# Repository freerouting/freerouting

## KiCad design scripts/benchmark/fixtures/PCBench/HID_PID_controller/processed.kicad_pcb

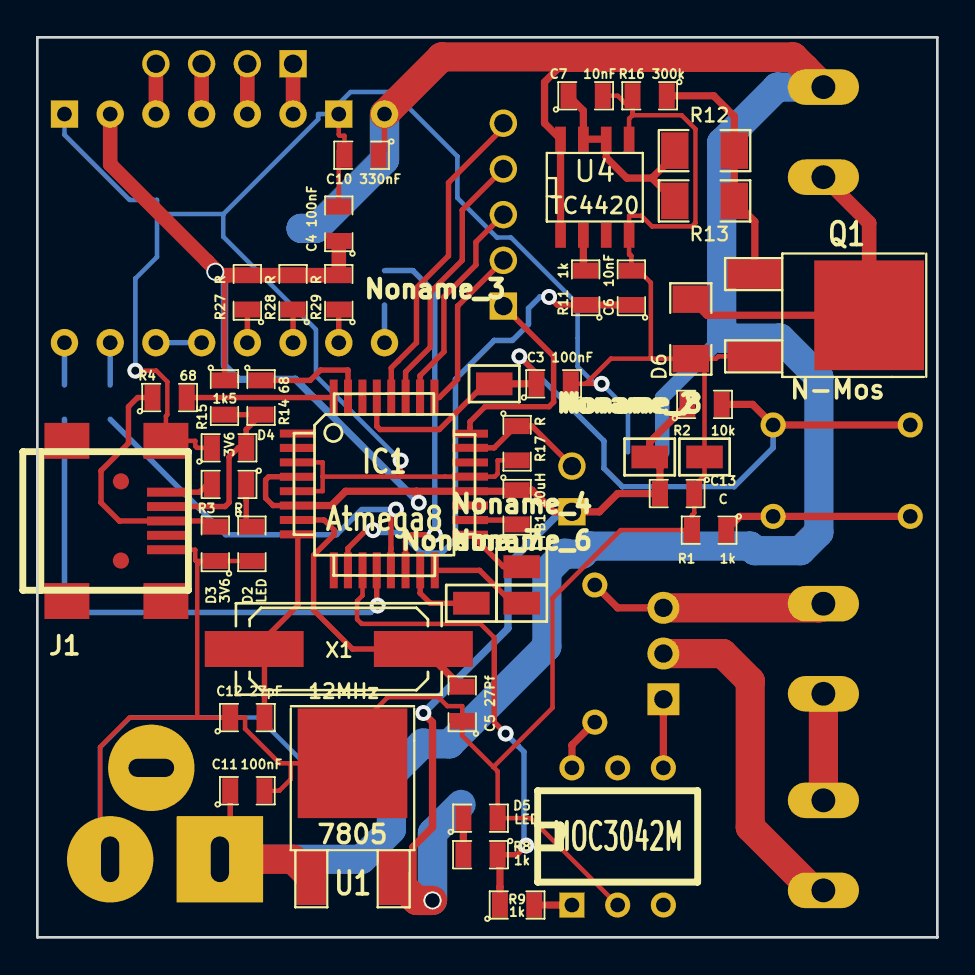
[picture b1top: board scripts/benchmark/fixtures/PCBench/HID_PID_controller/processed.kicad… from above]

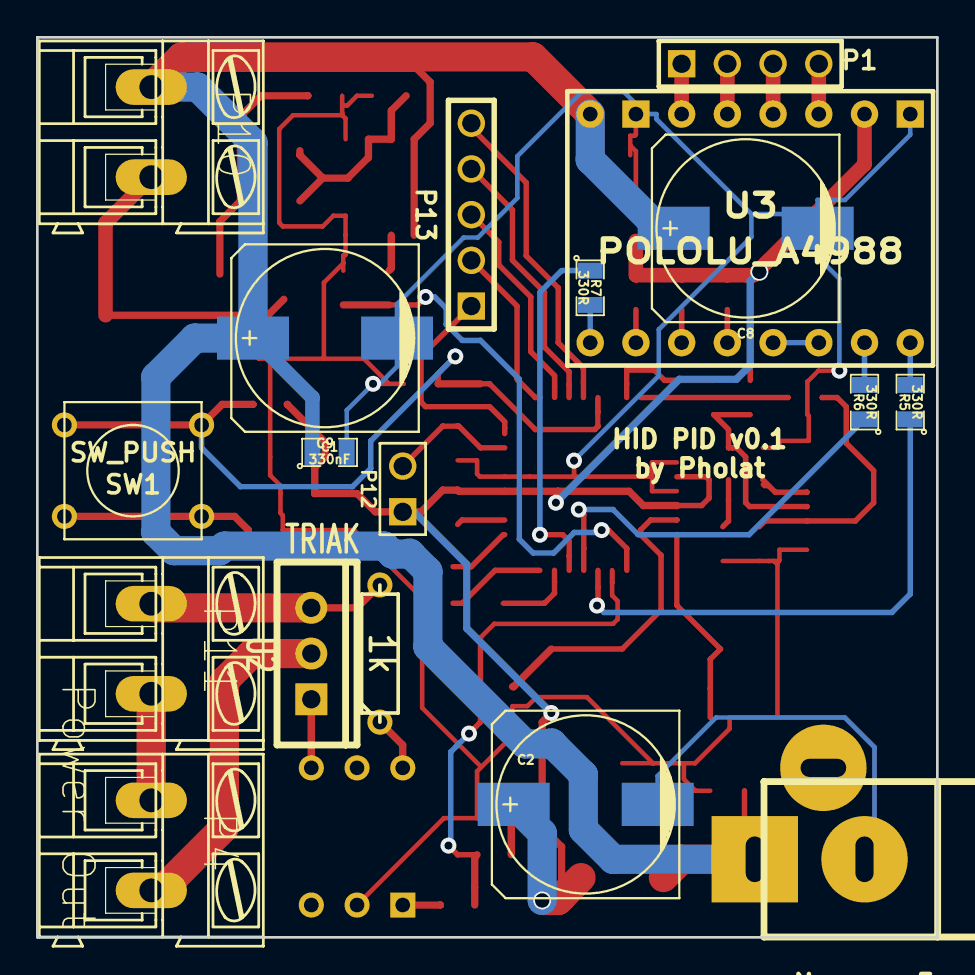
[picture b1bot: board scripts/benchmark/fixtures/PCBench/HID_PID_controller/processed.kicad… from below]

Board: 2 copper layers, 50.0 x 50.0 mm, 62 parts (18 on the bottom side), 50 nets.

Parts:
C1, C10: 330nF; SM0805
C2, C8, C9: 330uF; c_elec_10x10.5
C3, C4, C11: 100nF; SM0805
C5: 27Pf; SM0805
C6, C7: 10nF; SM0805
C12: 27pF; SM0805
C13: C; SM0805
D2, D5: LED; SM0805
D3, D4: 3V6; SM0805
D6: DIODE; SM1206
FB1: 10uH; SM0805
IC1: Atmega8; TQFP32
J1: USB; USB_MINI_B
Noname_1: MOC3042M; DIP-6__300
Noname_2, Noname_3, Noname_4, Noname_6, Noname_7, Noname_8: SMD_PIN
Noname_5: JACK_ALIM
P1: PIN_ARRAY_4x1
P4: Power Out; AK300-2
P10, P11: AK300-2
P12: NTC; PIN_ARRAY_2X1
P13: CONN_5; PIN_ARRAY_5x1
Q1: N-Mos; DPAKGDS
R1, R8, R9, R11: 1k; SM0805
R2: 10k; SM0805
R3, R17, R27, R28, R29: R; SM0805
R4, R14: 68; SM0805
R5, R6, R7: 330R; SM0805
R10: 1k; R3
R12, R13: 47; SM1206
R15: 1k5; SM0805
R16: 300k; SM0805
SW1: SW_PUSH; SW_PUSH_SMALL
U1: 7805; DPAK2
U2: TRIAK; TO220_VERT
U3: POLOLU_A4988; SWDIP8_.6W
U4: TC4420; SO8E
X1: 12MHz; Q_49U3HMS

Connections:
/AC_Controll: IC1.11, R8.1, R9.1
/AVcc: FB1.2, IC1.18
/D+: D3.2, J1.3, R4.1
/D-: D4.2, J1.2, R14.2, R15.2
/DIR1: R5.2, U3.16
/EN1: R7.2, U3.9
/MISO: IC1.16, Noname_6.1
/MOSI: IC1.15, Noname_7.1
/PWM: C6.1, IC1.10, R11.1
/RES: C3.1, IC1.29, Noname_3.1, R2.2, SW1.2
/SCK: IC1.17, Noname_4.1
/STEP1: R6.2, U3.15
/TempCheck: IC1.23, P12.2, R17.1
GND: C1.2, C2.2, C3.2, C4.2, C5.1, C6.2, C7.2, C8.2, C9.2, C10.2, C11.2, C12.1, C13.1, D2.2, D3.1, D4.1, D5.2, D6.1, IC1.3, IC1.5, IC1.21, J1.5, J1.6, Noname_1.2, Noname_2.1, Noname_5.2, Q1.S, R1.2, R16.2, R17.2, U1.2, U3.1, U3.7, U4.4, U4.5
unnamed: C12.2, IC1.8, X1.1
unnamed: P4.2, U2.3
unnamed: P4.1, P11.2
unnamed: IC1.25, P13.2
unnamed: IC1.28, P13.5
unnamed: IC1.27, P13.4
unnamed: IC1.24, P13.1
unnamed: IC1.32, R4.2
unnamed: D6.2, P10.2, Q1.D
unnamed: C7.1, R12.1, R13.1, U4.6, U4.7
unnamed: R11.2, U4.2
unnamed: Q1.G, R12.2, R13.2, R16.1
unnamed: IC1.31, R14.1
unnamed: R1.1, SW1.1
unnamed: IC1.26, P13.3
unnamed: C5.2, IC1.7, X1.2
unnamed: IC1.14, R7.1
unnamed: IC1.13, R6.1
unnamed: IC1.12, R5.1
unnamed: D2.1, R3.1
unnamed: J1.1, R3.2
unnamed: R27.1, U3.12
unnamed: R28.1, U3.11
unnamed: R29.1, U3.10
unnamed: P1.1, U3.6
unnamed: P1.2, U3.5
unnamed: P1.3, U3.4
unnamed: P1.4, U3.3
unnamed: P11.1, R10.2, U2.2
unnamed: Noname_1.6, R10.1
unnamed: Noname_1.4, U2.1
unnamed: Noname_1.1, R9.2
unnamed: D5.1, R8.2
unnamed: U3.13, U3.14
VAA: C1.1, C8.1, C9.1, C10.1, C11.1, Noname_5.1, P10.1, U1.1, U3.8, U4.1, U4.8
VCC: C2.1, C4.1, C13.2, FB1.1, IC1.4, IC1.6, IC1.20, Noname_8.1, P12.1, R2.1, R15.1, R27.2, R28.2, R29.2, U1.3, U3.2

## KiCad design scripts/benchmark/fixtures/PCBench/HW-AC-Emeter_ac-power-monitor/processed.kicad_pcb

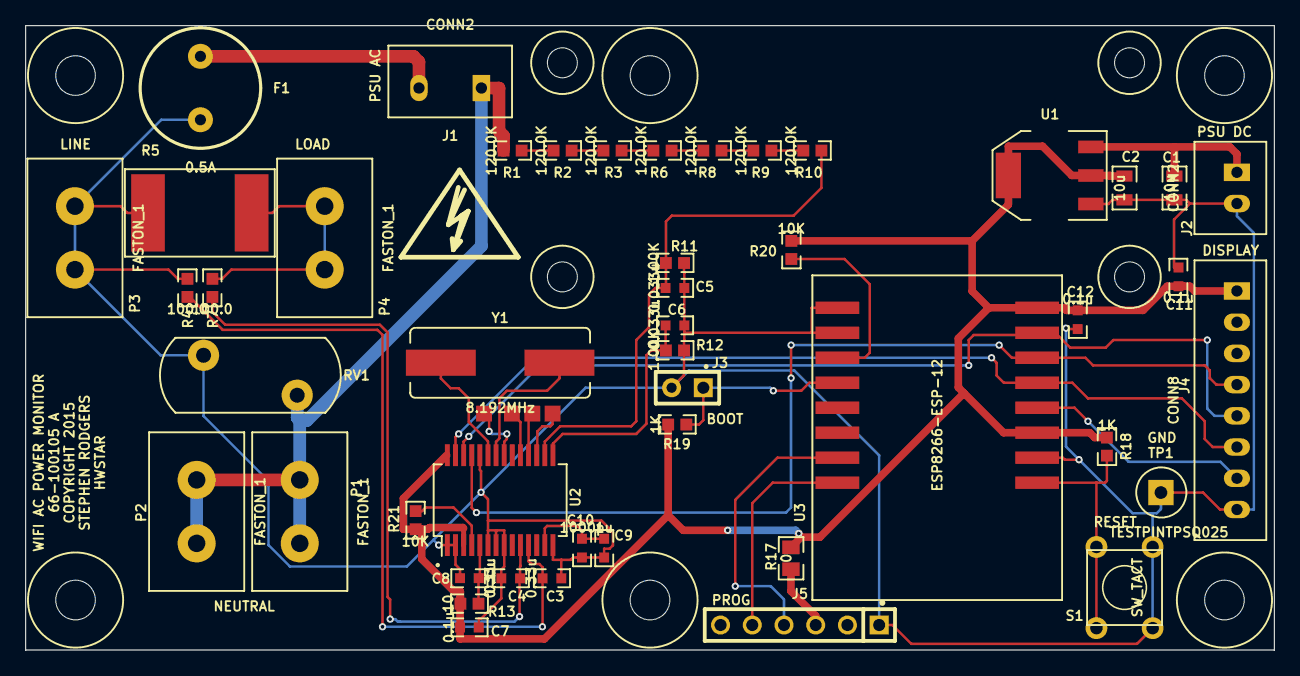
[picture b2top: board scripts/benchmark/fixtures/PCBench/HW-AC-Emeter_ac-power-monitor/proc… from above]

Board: 2 copper layers, 100.0 x 50.0 mm, 62 parts (0 on the bottom side), 35 nets.

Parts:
C1, C2: 10u; CC0805
C3, C4: 0.33u; CC0603
C5, C6: 0.033u; CC0603
C7, C8, C11, C12: 0.1u; CC0603
C9: 1u; CC0603
C10: 1000p; CC0603
F1: 0.5A; BELFUSE_MRT
J1: CONN2; JST_B3B_SPECIAL
J2: CONN2; JST_B2B_XH_A
J3: CONN2; BERG2
J4: CONN8; JST_B8B_XH_A
J5: CONN6; BERG6
MTG-HOLE-125-RING-300, MTG-HOLE-125-RING-300_2, MTG-HOLE-125-RING-300_3, MTG-HOLE-125-RING-300_4, MTG-HOLE-125-RING-300_5, MTG-HOLE-125-RING-300_6: VAL**; MTG-HOLE-125-RING-300
MTG-HOLE-M2-RING-5MM, MTG-HOLE-M2-RING-5MM_2, MTG-HOLE-M2-RING-5MM_3, MTG-HOLE-M2-RING-5MM_4: VAL**; MTG-HOLE-M2-RING-5MM
P1, P2, P3, P4: FASTON_1; KEYSTONE_1287-ST
R1, R2, R3, R6, R8, R9, R10: 120.0K; RC0603
R4, R7: 100.0; RC0603
R5: 0.001; WSL3921
R11, R12: 1.00K; RC0603
R13: 10; RC0603
R17: 0; RC0805
R18, R19: 1K; RC0603
R20, R21: 10K; RC0603
RV1: MOV-10D431; VARISTOR-10D
S1: SW_TACT; SW_TACT_6MM
Sym: Symbol_HighVoltage_Type2_SilkTop_VerySmall
TP1: TESTPINTPSQ025; TESTPIN
TP2, TP3, TP4, TP5: TESTPINTPSQ025; TESTPAD
U1: AZ1117CH-3.3TRG1; SOT-223-SAR
U2: 90E24PYGI; SSOP28-SAR
U3: ESP8266-ESP-12; ESP8266-ESP12
Y1: 8.192MHz; HC49US-SAR

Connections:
+3.3V: C2.1, C7.1, C11.1, C12.1, J4.1, R13.1, R17.1, R18.1, R19.1, R20.1, R21.1, U1.2, U1.4, U2.3, U2.28, U3.3, U3.8
/Power/+5V: C1.1, J2.1, U1.3
/Power/HOT: F1.2, J1.2
/Power/LOAD: P4.1, P4.2, R5.2, R7.2
/Power/NEUTRAL: J1.1, P1.1, P1.2, P2.1, P2.2, R1.1, RV1.1
/WIFI/GPIO16: J4.7, U3.4
/WIFI/SPWR: J5.3, R17.2
GND: C1.2, C2.2, C3.2, C4.1, C5.2, C6.2, C7.2, C8.2, C9.2, C10.2, C11.2, C12.2, F1.1, J2.2, J3.2, J4.8, J5.1, P3.1, P3.2, R4.2, R5.1, R11.2, R12.2, RV1.2, S1.1, S1.2, TP1.1, U1.1, U2.1, U2.2, U2.6, U2.7, U2.8, U2.14, U2.24, U3.2, U3.9, U3.10
ISAMPLEN: C3.1, R4.1, U2.11
ISAMPLEP: C4.2, R7.1, U2.10
unnamed: C8.1, R13.2, U2.5
unnamed: C9.1, C10.1, U2.13
unnamed: J3.1, R19.2, U3.12
unnamed: J5.4, U3.15
unnamed: J5.5, U3.16
unnamed: R1.2, R2.1
unnamed: R2.2, R3.1
unnamed: R3.2, R6.1
unnamed: R6.2, R8.1
unnamed: R8.2, R9.1
unnamed: R9.2, R10.1
unnamed: R18.2, S1.3, S1.4, U3.1
unnamed: R20.2, U3.11
unnamed: R21.2, U2.4
unnamed: TP2.1, U2.18
unnamed: TP3.1, U2.19
unnamed: TP4.1, U2.21
unnamed: TP5.1, U2.17
unnamed: U2.22, Y1.2
unnamed: U2.23, Y1.1
SCLK: J4.4, U2.25, U3.6
SDI: J4.6, U2.27, U3.5
SDO: J4.5, U2.26, U3.7
VSAMPLEN: C6.1, R12.1, U2.15
VSAMPLEP: C5.1, R10.2, R11.1, U2.16

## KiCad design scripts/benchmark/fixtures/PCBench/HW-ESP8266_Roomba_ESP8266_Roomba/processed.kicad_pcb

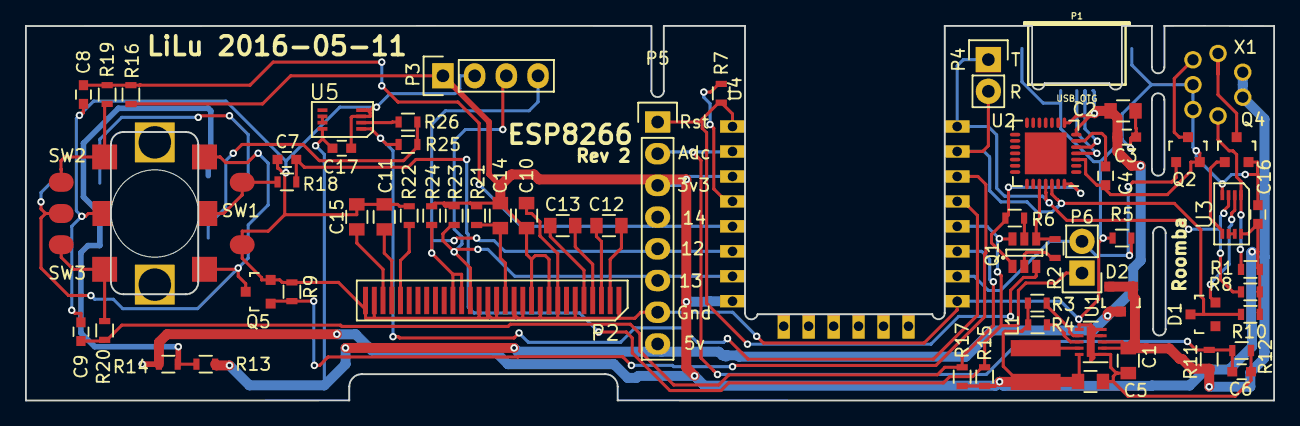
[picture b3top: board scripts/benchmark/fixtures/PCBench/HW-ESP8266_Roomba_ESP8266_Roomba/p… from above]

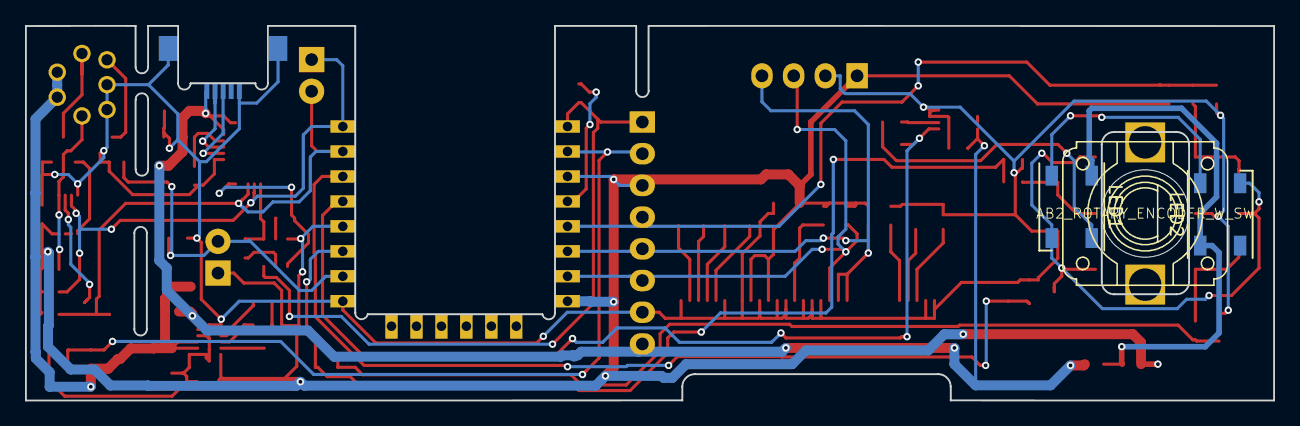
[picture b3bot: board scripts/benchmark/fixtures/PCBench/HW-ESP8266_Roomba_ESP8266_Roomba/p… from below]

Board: 2 copper layers, 100.0 x 30.0 mm, 68 parts (3 on the bottom side), 50 nets.

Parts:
C1, C11, C14, C15: 2u2; C_0805
C2, C10, C12, C13: 1u; C_0805
C3, C4, C6, C7, C8, C9, C16, C17: 100n; C_0603
C5: 22u; C_0805
D1, D2: MMBD717LT1G; SOT-23
L1: VLS4012ET-100M
LED1, LED2: WS2812B; LED_WS2812B-PLCC4
P1: USB_OTG; conn_usb_B_micro_smd-backside
P2: UG_62864
P3: CONN_01X04; Pin_Header_Straight_1x04
P4, P6: CONN_01X02; Pin_Header_Straight_1x02
P5: CONN_01X08; Pin_Header_Straight_1x08
Q1: DMC204010R; SOT-23-6
Q2, Q4, Q5: 2N7002; SOT-23
R1: 1M; R_0603
R2, R6, R7, R15, R16, R17, R21, R23, R24: 10k; R_0603
R3, R4, R5, R8, R9, R10: 100k; R_0603
R11: 470k; R_0603
R12: 18k; R_0603
R13, R14, R25, R26: 0R; R_0603
R18, R19, R20: 1k; R_0603
R22: 390k; R_0603
ROT_ENC1: AB2_ROTARY_ENCODER_W_SW; ROT_ENC_backside
SW1, SW2, SW3: SW_PUSH; switch3x6_smd
U1: TPS62177; DFN-10-1EP_2x3mm_Pitch0.5mm
U2: CP2102; QFN-28-1EP_5x5mm_Pitch0.5mm
U3, U5: 74LVC3G14; VSSOP-8
U4: ESP-12E; ESP-12E_SideMounted
X1: MINI_DIN_7; MiniDin-7

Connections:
+3V3: C5.1, C10.1, C14.1, C16.1, L1.2, P2.9, P2.11, P3.1, P5.3, R1.2, R3.1, R4.1, R8.1, R10.1, R14.1, R15.2, R16.2, R17.2, R21.2, R23.2, R24.2, U1.10, U3.8, U4.8
+12V: C1.1, D2.1, D2.2, R11.1, U1.2, U1.3, X1.1, X1.2
/5V: C2.1, C3.1, C17.1, D2.3, P1.1, P5.8, R13.2, U2.7, U2.8, U5.8
/ADC: C6.1, P5.2, R11.2, R12.1, U4.2
/DTR: Q1.1, R6.1, U2.28
/Enc_A: C9.1, R17.1, R20.2, U4.17
/Enc_B: C8.1, P5.4, R16.1, R19.2, U4.5
/LED: R25.2, U4.19, U5.1
/PowerOn: Q5.1, R9.2, U4.20
/RST: P5.1, Q1.3, R7.2, U4.1
/RTS: Q1.4, R2.1, U2.24
/RXD: D1.3, P4.2, R10.2, U2.26, U4.21
/Roomba_Wake: P6.2, Q2.1, R5.2, U4.16
/SCL: P2.18, P3.3, P5.6, R23.1, U4.7
/SDA: P2.19, P2.20, P3.4, P5.5, R24.1, U4.6
/Switch: C7.1, P6.1, Q1.6, R15.1, R18.2, U4.18
/TXD: P4.1, R8.2, U2.25, U3.3, U4.22
GND: C1.2, C2.2, C3.2, C4.2, C5.2, C6.2, C7.2, C8.2, C9.2, C11.2, C14.2, C15.2, C16.2, C17.2, P1.5, P1.6, P2.1, P2.6, P2.8, P2.10, P2.12, P2.13, P2.15, P2.16, P2.17, P2.29, P2.30, P3.2, P5.7, Q2.2, Q4.2, Q5.2, R5.1, R9.1, R12.2, R22.2, ROT_ENC1.6, SW1.2, U1.1, U1.4, U1.5, U1.6, U1.11, U2.3, U3.4, U4.15, U5.3, U5.4, X1.6, X1.7
GNDPWR: LED1.3, LED2.3, Q5.3, ROT_ENC1.2, SW2.2, SW3.2
unnamed: C4.1, U2.6
unnamed: C10.2, P2.14, R21.1
unnamed: C11.1, P2.27
unnamed: C12.1, P2.2
unnamed: C12.2, P2.3
unnamed: C13.1, P2.4
unnamed: C13.2, P2.5
unnamed: C15.1, P2.28
unnamed: D1.2, U3.2
unnamed: L1.1, U1.9
unnamed: LED1.1, LED2.1, R13.1, R14.2
unnamed: LED1.2, LED2.4
unnamed: LED1.4, R25.1, R26.1
unnamed: P1.2, U2.5
unnamed: P1.3, U2.4
unnamed: P2.26, R22.1
unnamed: Q1.2, R2.2
unnamed: Q1.5, R6.2
unnamed: Q2.3, X1.5
unnamed: Q4.1, U3.5
unnamed: Q4.3, X1.3
unnamed: R1.1, U3.1, X1.4
unnamed: R3.2, U1.7
unnamed: R4.2, U1.8
unnamed: R7.1, U4.4
unnamed: R18.1, ROT_ENC1.4, SW1.1
unnamed: R19.1, ROT_ENC1.3, SW2.1
unnamed: R20.1, ROT_ENC1.1, SW3.1
unnamed: R26.2, U5.2
unnamed: U3.6, U3.7
unnamed: U5.6, U5.7

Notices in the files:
scripts/benchmark/fixtures/PCBench/HW-AC-Emeter_ac-power-monitor/processed.kicad_pcb:
COPYRIGHT 2015
